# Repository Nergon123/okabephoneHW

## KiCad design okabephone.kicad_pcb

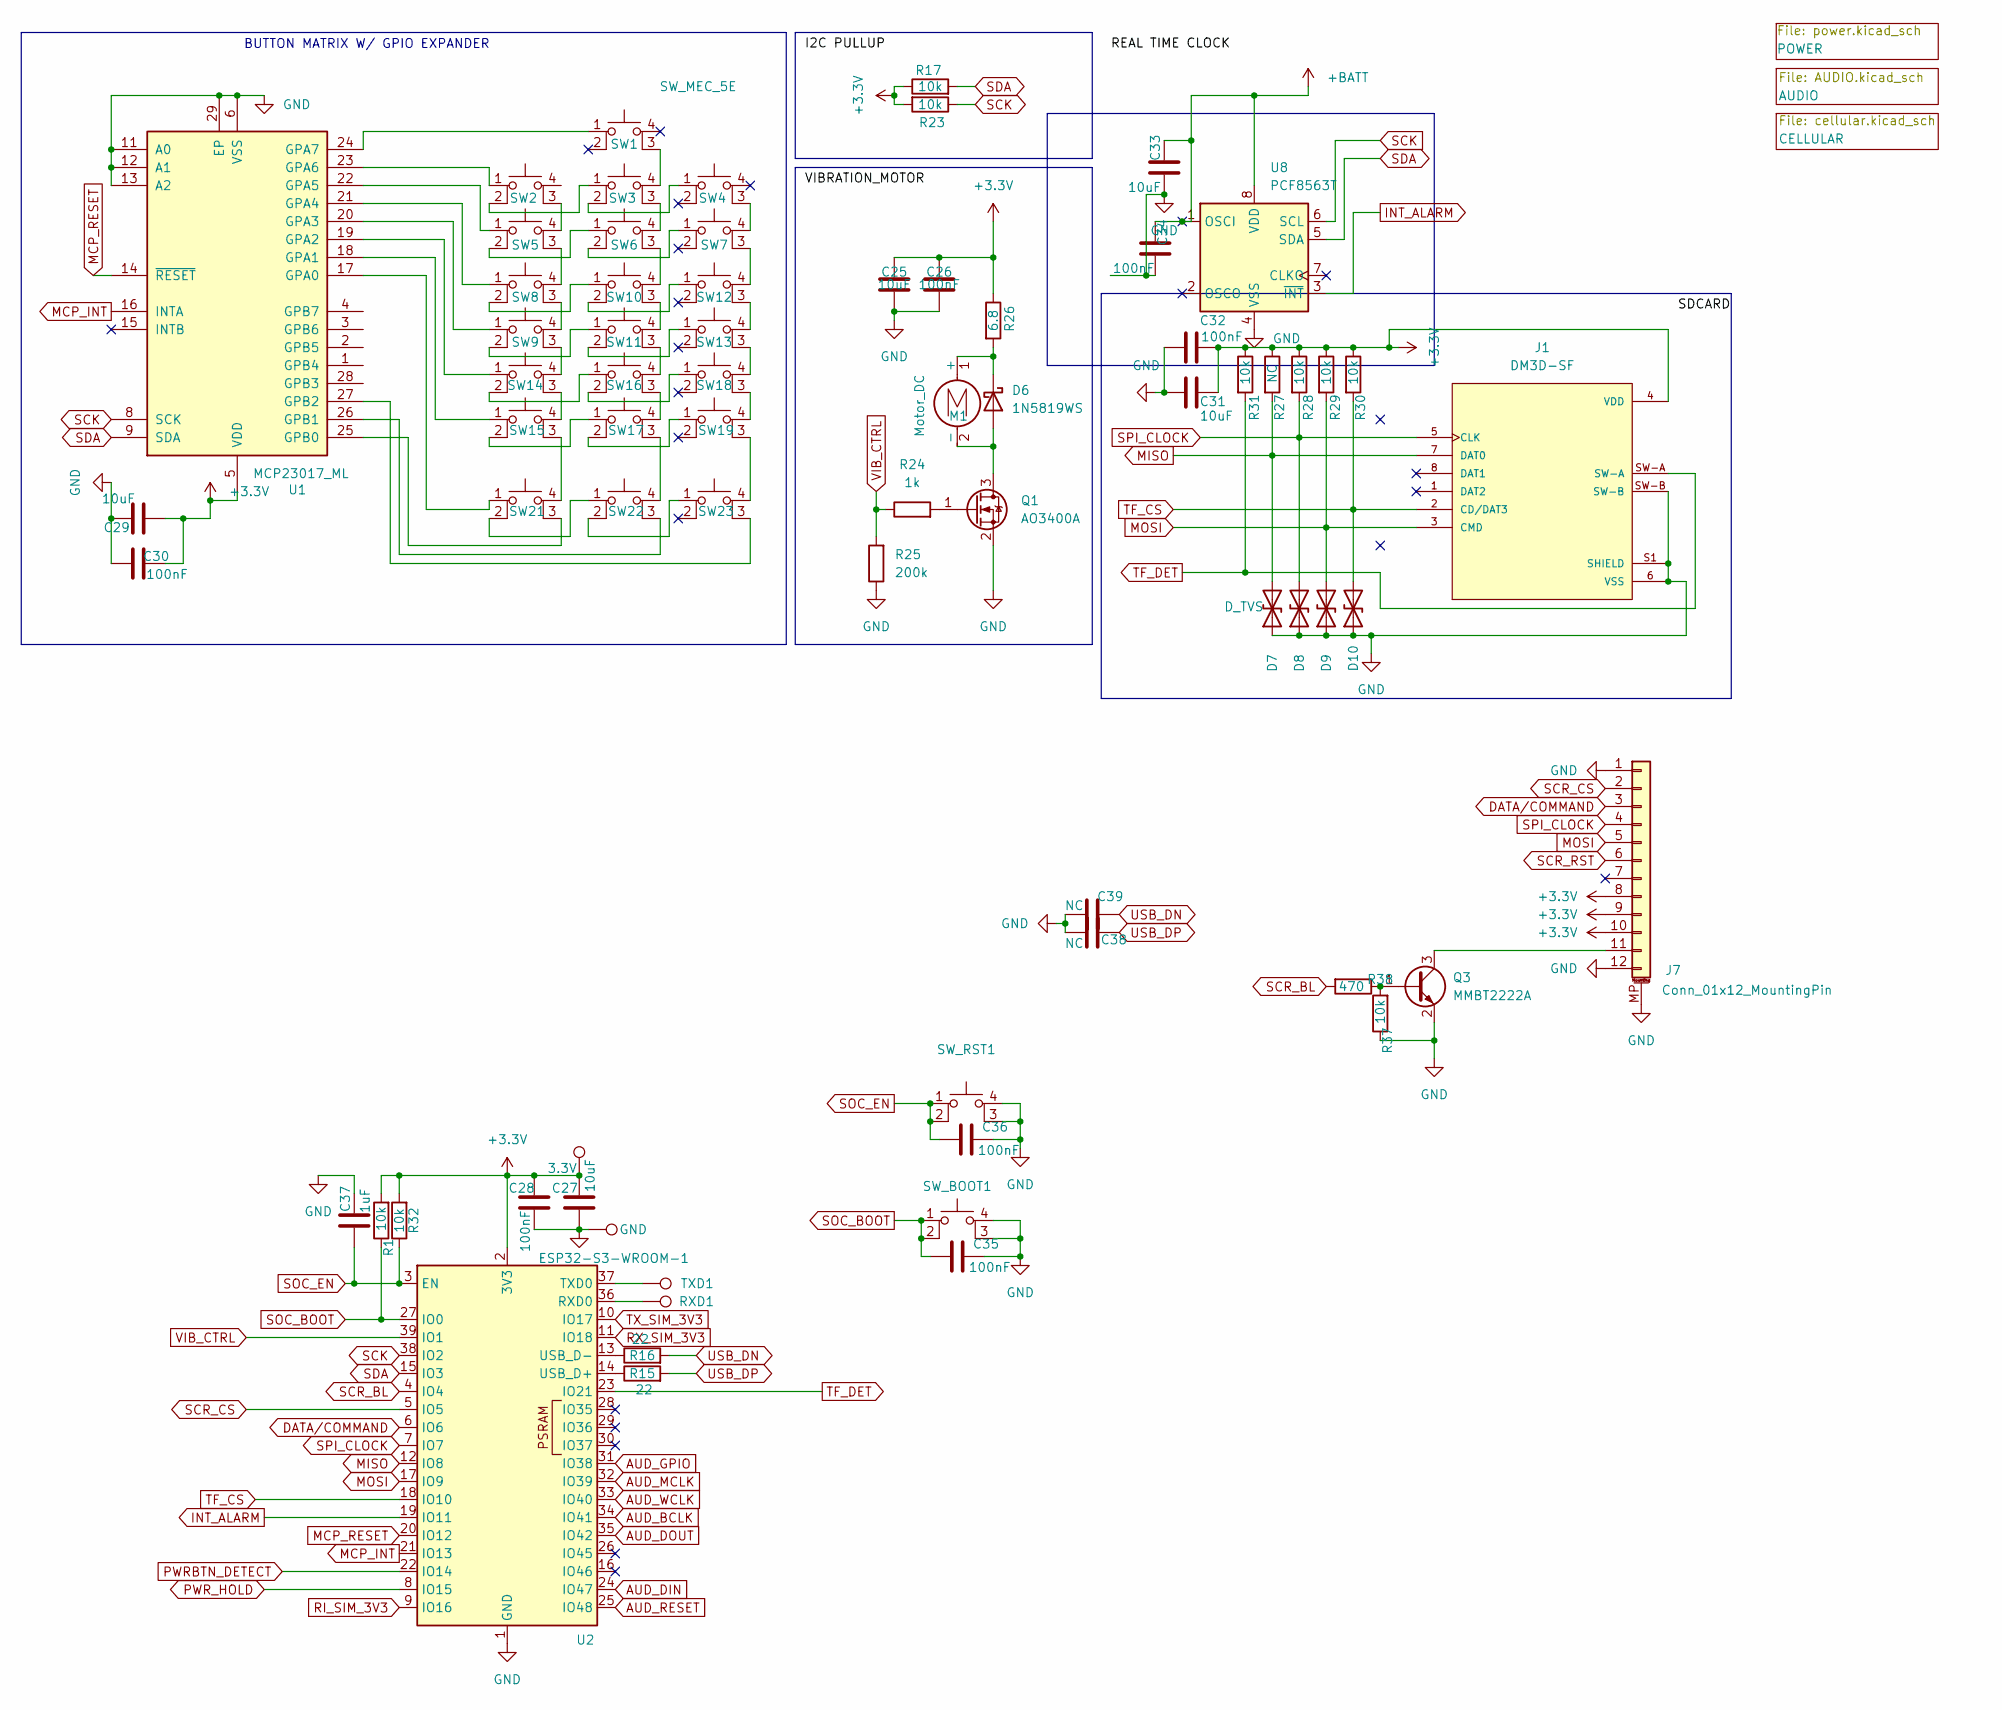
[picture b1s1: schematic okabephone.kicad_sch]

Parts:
C25, C27, C29, C31, C33: 10uF; C_0603_1608Metric_Pad1.08x0.95mm_HandSolder
C26, C28, C30, C32, C34, C35, C36: 100nF; C_0603_1608Metric_Pad1.08x0.95mm_HandSolder
C37: 1uF; C_0603_1608Metric_Pad1.08x0.95mm_HandSolder
C38, C39: NC; C_0603_1608Metric_Pad1.08x0.95mm_HandSolder
D6: 1N5819WS; D_SOD-323
D7, D8, D9, D10: D_TVS; D_0603_1608Metric_Pad1.05x0.95mm_HandSolder
J1: DM3D-SF; HRS_DM3D-SF; PARTREV 2017.1
J7: Conn_01x12_MountingPin; TE_1-1734839-2_1x12-1MP_P0.5mm_Horizontal
M1: Motor_DC; JST_EH_B2B-EH-A_1x02_P2.50mm_Vertical
Q1: AO3400A; SOT-23
Q3: MMBT2222A; SOT-23
R1, R17, R23, R28, R29, R30, R31, R32, R37: 10k; R_0603_1608Metric_Pad0.98x0.95mm_HandSolder
R15, R16: 22; R_0603_1608Metric_Pad0.98x0.95mm_HandSolder
R24: 1k; R_0603_1608Metric_Pad0.98x0.95mm_HandSolder
R25: 200k; R_0603_1608Metric_Pad0.98x0.95mm_HandSolder
R26: 6.8; R_0603_1608Metric_Pad0.98x0.95mm_HandSolder
R27: NC; R_0603_1608Metric_Pad0.98x0.95mm_HandSolder
R38: 470; R_0603_1608Metric_Pad0.98x0.95mm_HandSolder
RXD1: TestPoint; TestPoint_Pad_D1.0mm
SW1, SW2, SW3, SW4, SW5, SW6, SW7, SW8, SW9, SW10, SW11, SW12, SW13, SW14, SW15, SW16, SW17, SW18, SW19, SW21, SW22, SW23: SW_MEC_5E; SW_PTS526_SM08_SMTR2_LFS
SW_BOOT1: SW_MEC_5E; SW_PTS526_SM08_SMTR2_LFS
SW_RST1: SW_MEC_5E; SW_PTS526_SM08_SMTR2_LFS
TP8: 3.3V; TestPoint_Pad_D1.0mm
TP9: GND; TestPoint_Pad_D1.0mm
TXD1: TestPoint; TestPoint_Pad_D1.0mm
U1: MCP23017_ML; QFN-28-1EP_6x6mm_P0.65mm_EP4.25x4.25mm
U2: ESP32-S3-WROOM-1
U8: PCF8563T; SOIC-8_3.9x4.9mm_P1.27mm

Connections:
+3.3V: C25.2, C26.2, C27.2, C28.2, C29.2, C30.2, C31.2, C32.2, J1.4 (VDD), J7.8, J7.9, J7.10, R1.2, R17.1, R23.2, R26.1, R27.1, R28.1, R29.1, R30.1, R31.1, R32.2, TP8.1, U1.5 (VDD), U2.2 (3V3); also elsewhere on the board
+BATT: C33.2, C34.2, U8.1 (OSCI), U8.8 (VDD); also elsewhere on the board
AUD_BCLK: U2.34 (IO41); also elsewhere on the board
AUD_DIN: U2.24 (IO47); also elsewhere on the board
AUD_DOUT: U2.35 (IO42); also elsewhere on the board
AUD_GPIO: U2.31 (IO38); also elsewhere on the board
AUD_MCLK: U2.32 (IO39); also elsewhere on the board
AUD_RESET: U2.25 (IO48); also elsewhere on the board
AUD_WCLK: U2.33 (IO40); also elsewhere on the board
DATA/COMMAND: J7.3, U2.6 (IO6)
GND: C25.1, C26.1, C27.1, C28.1, C29.1, C30.1, C31.1, C32.1, C33.1, C34.1, C35.1, C36.1, C37.1, C38.1, C39.1, D7.1 (A1), D8.1 (A1), D9.1 (A1), D10.1 (A1), J1.6 (VSS), J1.S1 (SHIELD), J1.S2 (SHIELD), J1.S3 (SHIELD), J1.S4 (SHIELD), J1.SW-B, J7.1, J7.12, J7.MP (MountPin), Q1.2 (S), Q3.2 (E), R25.1, R37.1, SW_BOOT1.3 (K), SW_BOOT1.4 (A), SW_RST1.3 (K), SW_RST1.4 (A), TP9.1, U1.6 (VSS), U1.11 (A0), U1.12 (A1), U1.13 (A2), U1.29 (EP), U2.1 (GND), U2.40 (GND), U2.41 (GND), U8.4 (VSS); also elsewhere on the board
INT_ALARM: U2.19 (IO11), U8.3 (~INT)
MCP_INT: U1.16 (INTA), U2.21 (IO13)
MCP_RESET: U1.14 (~RESET), U2.20 (IO12)
MISO: D7.2 (A2), J1.7 (DAT0), R27.2, U2.12 (IO8)
MOSI: D9.2 (A2), J1.3 (CMD), J7.5, R29.2, U2.17 (IO9)
unnamed: D6.2 (A), M1.2 (-), Q1.3 (D)
unnamed: D6.1 (K), M1.1 (+), R26.2
unnamed: J7.11, Q3.3 (C)
unnamed: Q1.1 (G), R24.2
unnamed: Q3.1 (B), R37.2, R38.1
unnamed: SW1.3 (K), SW3.4 (A)
unnamed: SW2.3 (K), SW5.4 (A)
unnamed: SW2.2, SW3.1
unnamed: SW3.3 (K), SW6.4 (A)
unnamed: SW3.2, SW4.1
unnamed: SW4.3 (K), SW7.4 (A)
unnamed: SW5.3 (K), SW8.4 (A)
unnamed: SW5.2, SW6.1
unnamed: SW6.2, SW7.1
unnamed: SW8.3 (K), SW9.4 (A)
unnamed: SW6.3 (K), SW10.4 (A)
unnamed: SW10.3 (K), SW11.4 (A)
unnamed: SW8.2, SW10.1
unnamed: SW10.2, SW12.1
unnamed: SW11.3 (K), SW16.4 (A)
unnamed: SW9.2, SW11.1
unnamed: SW11.2, SW13.1
unnamed: SW7.3 (K), SW12.4 (A)
unnamed: SW12.3 (K), SW13.4 (A)
unnamed: SW13.3 (K), SW18.4 (A)
unnamed: SW9.3 (K), SW14.4 (A)
unnamed: SW14.3 (K), SW15.4 (A)
unnamed: SW14.2, SW16.1
unnamed: SW15.3 (K), SW21.4 (A)
unnamed: SW15.2, SW17.1
unnamed: SW16.3 (K), SW17.4 (A)
unnamed: SW16.2, SW18.1
unnamed: SW17.3 (K), SW22.4 (A)
unnamed: SW17.2, SW19.1
unnamed: SW18.3 (K), SW19.4 (A)
unnamed: SW19.3 (K), SW23.4 (A)
unnamed: SW21.3 (K), U1.25 (GPB0)
unnamed: SW21.2, SW22.1
unnamed: SW22.3 (K), U1.26 (GPB1)
unnamed: SW22.2, SW23.1
unnamed: SW23.3 (K), U1.27 (GPB2)
unnamed: SW21.1, U1.17 (GPA0)
unnamed: SW15.1, U1.18 (GPA1)
unnamed: SW14.1, U1.19 (GPA2)
unnamed: SW9.1, U1.20 (GPA3)
unnamed: SW8.1, U1.21 (GPA4)
unnamed: SW5.1, U1.22 (GPA5)
unnamed: SW2.1, U1.23 (GPA6)
unnamed: SW1.1, U1.24 (GPA7)
unnamed: RXD1.1, U2.36 (RXD0)
unnamed: TXD1.1, U2.37 (TXD0)
unnamed: R15.1, U2.14 (USB_D+)
unnamed: R16.1, U2.13 (USB_D-)
PWRBTN_DETECT: U2.22 (IO14); also elsewhere on the board
PWR_HOLD: U2.8 (IO15); also elsewhere on the board
RI_SIM_3V3: U2.9 (IO16); also elsewhere on the board
RX_SIM_3V3: U2.11 (IO18); also elsewhere on the board
SCK: R23.1, U1.8 (SCK), U2.38 (IO2), U8.6 (SCL); also elsewhere on the board
SCR_BL: R38.2, U2.4 (IO4)
SCR_CS: J7.2, U2.5 (IO5)
SCR_RST: J7.6
SDA: R17.2, U1.9 (SDA), U2.15 (IO3), U8.5 (SDA); also elsewhere on the board
SOC_BOOT: C35.2, R1.1, SW_BOOT1.1, SW_BOOT1.2, U2.27 (IO0)
SOC_EN: C36.2, C37.2, R32.1, SW_RST1.1, SW_RST1.2, U2.3 (EN)
SPI_CLOCK: D8.2 (A2), J1.5 (CLK), J7.4, R28.2, U2.7 (IO7)
TF_CS: D10.2 (A2), J1.2 (CD/DAT3), R30.2, U2.18 (IO10)
TF_DET: J1.SW-A, R31.2, U2.23 (IO21)
TX_SIM_3V3: U2.10 (IO17); also elsewhere on the board
USB_DN: C39.2, R16.2; also elsewhere on the board
USB_DP: C38.2, R15.2; also elsewhere on the board
VIB_CTRL: R24.1, R25.2, U2.39 (IO1)

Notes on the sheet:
BUTTON MATRIX W/ GPIO EXPANDER

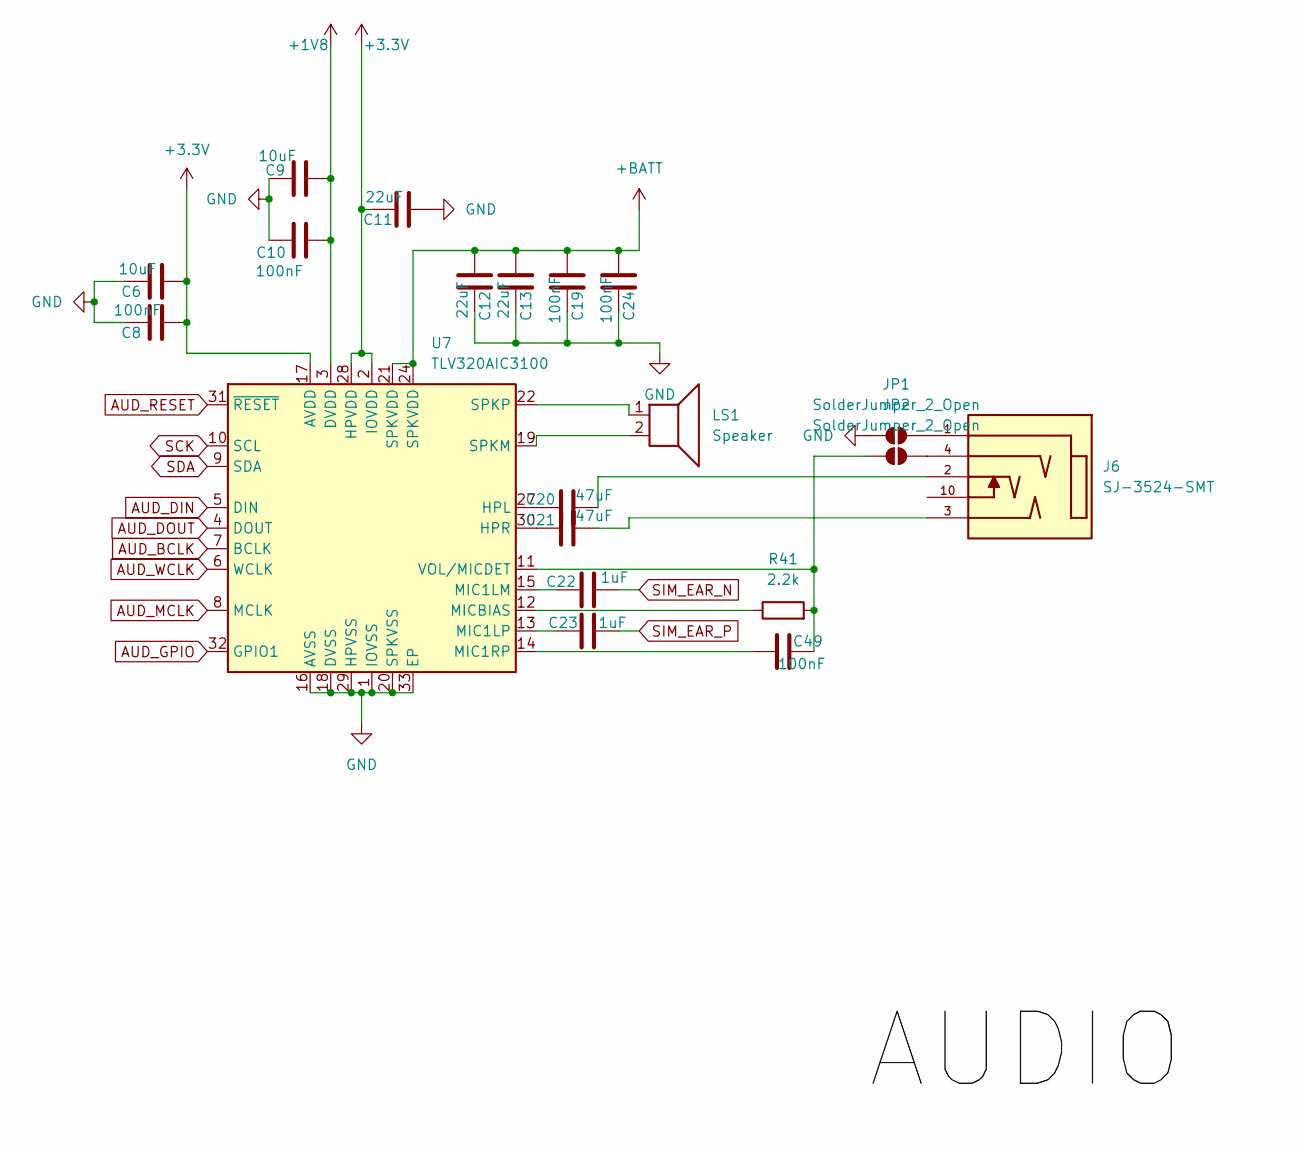
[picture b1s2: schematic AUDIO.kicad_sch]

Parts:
C6, C9: 10uF; C_0603_1608Metric_Pad1.08x0.95mm_HandSolder
C8, C10, C19, C24, C49: 100nF; C_0603_1608Metric_Pad1.08x0.95mm_HandSolder
C11, C12, C13: 22uF; C_0603_1608Metric_Pad1.08x0.95mm_HandSolder
C20, C21: 47uF; C_0603_1608Metric_Pad1.08x0.95mm_HandSolder
C22, C23: 1uF; C_0603_1608Metric_Pad1.08x0.95mm_HandSolder
J6: SJ-3524-SMT; SWITCHCRAFT_35RASMT6CHNTRX; PARTREV A
JP1, JP2: SolderJumper_2_Open; SolderJumper-2_P1.3mm_Open_TrianglePad1.0x1.5mm
LS1: Speaker; JST_EH_B2B-EH-A_1x02_P2.50mm_Vertical
R41: 2.2k
U7: TLV320AIC3100; VQFN-32-1EP_5x5mm_P0.5mm_EP3.5x3.5mm

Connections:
+1V8: C9.2, C10.2, U7.3 (DVDD); also elsewhere on the board
+3.3V: C6.2, C8.2, C11.1, U7.2 (IOVDD), U7.17 (AVDD), U7.28 (HPVDD); also elsewhere on the board
+BATT: C12.2, C13.2, C19.2, C24.2, U7.21 (SPKVDD), U7.24 (SPKVDD); also elsewhere on the board
AUD_BCLK: U7.7 (BCLK); also elsewhere on the board
AUD_DIN: U7.5 (DIN); also elsewhere on the board
AUD_DOUT: U7.4 (DOUT); also elsewhere on the board
AUD_GPIO: U7.32 (GPIO1); also elsewhere on the board
AUD_MCLK: U7.8 (MCLK); also elsewhere on the board
AUD_RESET: U7.31 (~RESET); also elsewhere on the board
AUD_WCLK: U7.6 (WCLK); also elsewhere on the board
GND: C6.1, C8.1, C9.1, C10.1, C11.2, C12.1, C13.1, C19.1, C24.1, J6.1, JP1.1 (A), JP1.2 (B), U7.1 (IOVSS), U7.16 (AVSS), U7.18 (DVSS), U7.20 (SPKVSS), U7.25 (SPKVSS), U7.29 (HPVSS), U7.33 (EP); also elsewhere on the board
unnamed: C20.2, J6.2
unnamed: C21.2, J6.3
unnamed: C49.1, JP2.1 (A), R41.2, U7.11 (VOL/MICDET)
unnamed: C49.2, U7.14 (MIC1RP)
unnamed: J6.4, JP2.2 (B)
unnamed: LS1.1, U7.22 (SPKP), U7.26 (SPKP)
unnamed: LS1.2, U7.19 (SPKM), U7.23 (SPKM)
unnamed: R41.1, U7.12 (MICBIAS)
unnamed: C20.1, U7.27 (HPL)
unnamed: C21.1, U7.30 (HPR)
unnamed: C22.1, U7.15 (MIC1LM)
unnamed: C23.1, U7.13 (MIC1LP)
SCK: U7.10 (SCL); also elsewhere on the board
SDA: U7.9 (SDA); also elsewhere on the board
SIM_EAR_N: C22.2; also elsewhere on the board
SIM_EAR_P: C23.2; also elsewhere on the board

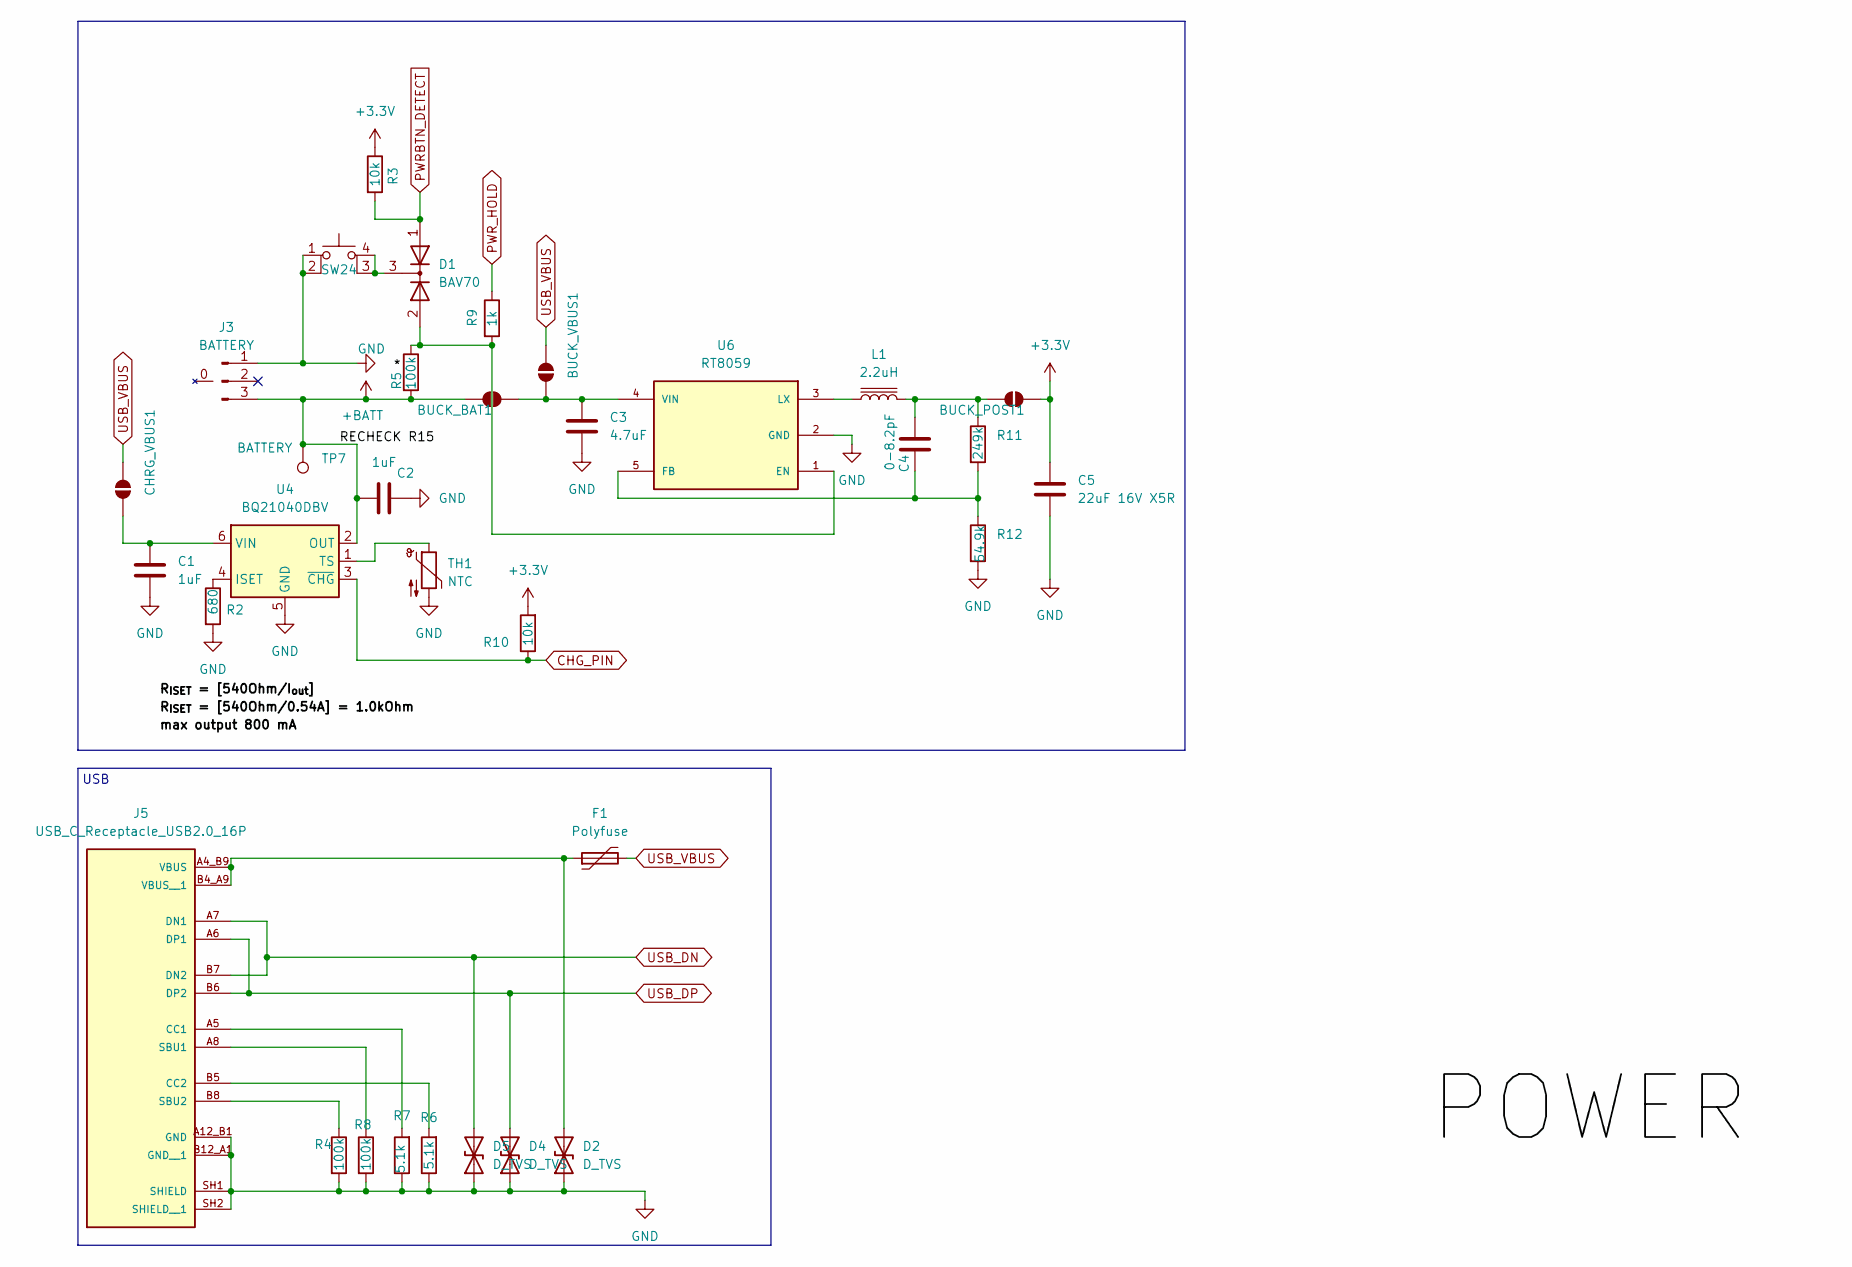
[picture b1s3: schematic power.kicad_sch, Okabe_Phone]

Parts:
BUCK_BAT1: SolderJumper_2_Open; SolderJumper-2_P1.3mm_Open_Pad1.0x1.5mm
BUCK_POST1: SolderJumper_2_Open; SolderJumper-2_P1.3mm_Open_Pad1.0x1.5mm
BUCK_VBUS1: SolderJumper_2_Open; SolderJumper-2_P1.3mm_Open_Pad1.0x1.5mm
C1, C2: 1uF; C_0603_1608Metric_Pad1.08x0.95mm_HandSolder
C3: 4.7uF; C_0603_1608Metric_Pad1.08x0.95mm_HandSolder
C4: 0-8.2pF; C_0603_1608Metric_Pad1.08x0.95mm_HandSolder
C5: 22uF 16V X5R; C_1206_3216Metric
CHRG_VBUS1: SolderJumper_2_Open; SolderJumper-2_P1.3mm_Open_Pad1.0x1.5mm
D1: BAV70; SOT-23
D2, D4, D5: D_TVS; D_0603_1608Metric_Pad1.05x0.95mm_HandSolder
F1: Polyfuse; Fuse_1210_3225Metric
J3: BATTERY; Battery connector 3mm nergon
J5: USB_C_Receptacle_USB2.0_16P; CUI_UJ20-C-G-MSMT-TR-68; PARTREV 1.0
L1: 2.2uH; L_6.3x6.3_H3
R2: 680; R_0603_1608Metric_Pad0.98x0.95mm_HandSolder
R3, R10: 10k; R_0603_1608Metric_Pad0.98x0.95mm_HandSolder
R4, R5, R8: 100k; R_0603_1608Metric_Pad0.98x0.95mm_HandSolder
R6, R7: 5.1k; R_0603_1608Metric_Pad0.98x0.95mm_HandSolder
R9: 1k; R_0603_1608Metric_Pad0.98x0.95mm_HandSolder
R11: 249k; R_0603_1608Metric_Pad0.98x0.95mm_HandSolder
R12: 54.9k; R_0603_1608Metric_Pad0.98x0.95mm_HandSolder
SW24: SW_MEC_5E; SW_PTS526_SM08_SMTR2_LFS
TH1: NTC; JST_EH_B2B-EH-A_1x02_P2.50mm_Vertical
TP7: BATTERY; TestPoint_Pad_D1.0mm
U4: BQ21040DBV; SOT-23-6
U6: RT8059; TSOT-23-5_HandSoldering

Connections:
+3.3V: BUCK_POST1.1 (A), C5.1, R3.1, R10.2; also elsewhere on the board
+BATT: BUCK_BAT1.2 (B), C2.1, J3.3, R5.2, TP7.1, U4.2 (OUT); also elsewhere on the board
CHG_PIN: R10.1, U4.3 (~CHG)
GND: C1.2, C2.2, C3.2, C5.2, D2.1 (A1), D4.1 (A1), D5.1 (A1), J3.1, J5.A12_B1 (GND), J5.B12_A1 (GND__1), J5.SH1 (SHIELD), J5.SH2 (SHIELD__1), R2.2, R4.2, R6.1, R7.1, R8.2, R12.2, SW24.1, SW24.2, TH1.2, U4.5 (GND), U6.2 (GND); also elsewhere on the board
unnamed: BUCK_BAT1.1 (A), BUCK_VBUS1.2 (B), C3.1, U6.4 (VIN)
unnamed: BUCK_POST1.2 (B), C4.1, L1.2, R11.1
unnamed: C1.1, CHRG_VBUS1.2 (B), U4.6 (VIN)
unnamed: D1.3 (K), SW24.3 (K), SW24.4 (A)
unnamed: D2.2 (A2), F1.1, J5.A4_B9 (VBUS), J5.B4_A9 (VBUS__1)
unnamed: J5.A5 (CC1), R7.2
unnamed: J5.B5 (CC2), R6.2
unnamed: J5.A8 (SBU1), R8.1
unnamed: J5.B8 (SBU2), R4.1
unnamed: R2.1, U4.4 (ISET)
unnamed: TH1.1, U4.1 (TS)
unnamed: D1.2 (A), R5.1, R9.2, U6.1 (EN)
unnamed: C4.2, R11.2, R12.1, U6.5 (FB)
unnamed: L1.1, U6.3 (LX)
PWRBTN_DETECT: D1.1 (A), R3.2; also elsewhere on the board
PWR_HOLD: R9.1; also elsewhere on the board
USB_DN: D5.2 (A2), J5.A7 (DN1), J5.B7 (DN2); also elsewhere on the board
USB_DP: D4.2 (A2), J5.A6 (DP1), J5.B6 (DP2); also elsewhere on the board
USB_VBUS: BUCK_VBUS1.1 (A), CHRG_VBUS1.1 (A), F1.2

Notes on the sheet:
USB

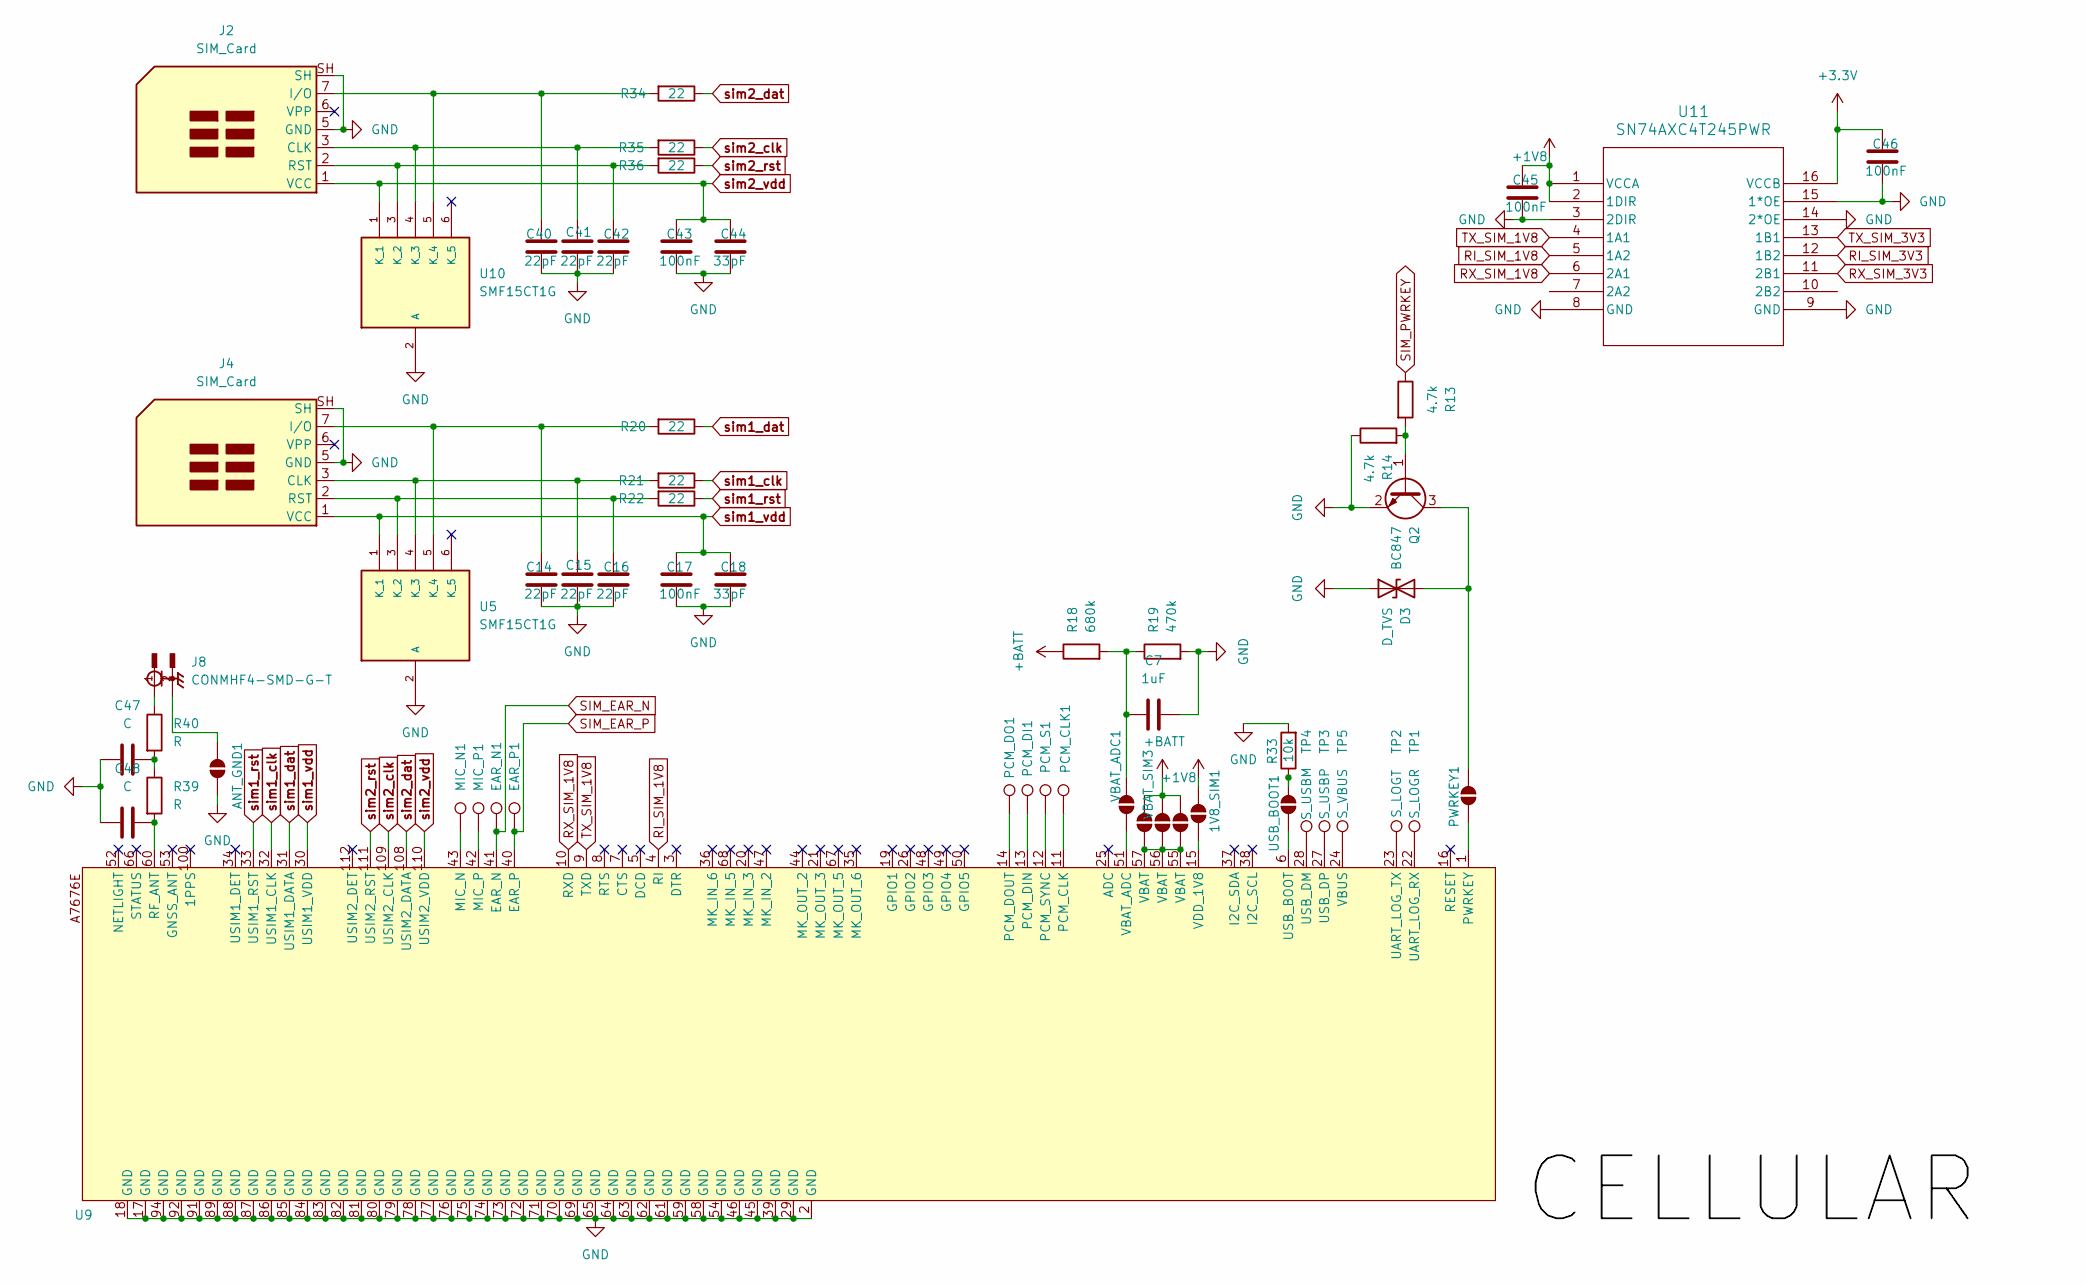
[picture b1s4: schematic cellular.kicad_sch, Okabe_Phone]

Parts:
1V8_SIM1: SolderJumper_2_Open; SolderJumper-2_P1.3mm_Open_Pad1.0x1.5mm
ANT_GND1: SolderJumper_2_Open; SolderJumper-2_P1.3mm_Open_Pad1.0x1.5mm
C7: 1uF; C_0603_1608Metric_Pad1.08x0.95mm_HandSolder
C14, C15, C16, C40, C41, C42: 22pF; C_0603_1608Metric_Pad1.08x0.95mm_HandSolder
C17, C43, C45, C46: 100nF; C_0603_1608Metric_Pad1.08x0.95mm_HandSolder
C18, C44: 33pF; C_0603_1608Metric_Pad1.08x0.95mm_HandSolder
C47, C48: C; C_0603_1608Metric_Pad1.08x0.95mm_HandSolder
D3: D_TVS; D_0603_1608Metric_Pad1.05x0.95mm_HandSolder
EAR_N1: TestPoint; TestPoint_Pad_D1.5mm
EAR_P1: TestPoint; TestPoint_Pad_D1.5mm
J2, J4: SIM_Card; nanoSIM_GCT_SIM8060-6-0-14-00
J8: CONMHF4-SMD-G-T; TE_CONMHF4-SMD-G-T; PARTREV A
MIC_N1: TestPoint; TestPoint_Pad_D1.5mm
MIC_P1: TestPoint; TestPoint_Pad_D1.5mm
PCM_CLK1: TestPoint; TestPoint_Pad_D1.0mm
PCM_DI1: TestPoint; TestPoint_Pad_D1.0mm
PCM_DO1: TestPoint; TestPoint_Pad_D1.0mm
PCM_S1: TestPoint; TestPoint_Pad_D1.0mm
PWRKEY1: SolderJumper_2_Open; SolderJumper-2_P1.3mm_Open_Pad1.0x1.5mm
Q2: BC847; SOT-23
R13, R14: 4.7k; R_0603_1608Metric_Pad0.98x0.95mm_HandSolder
R18: 680k; R_0603_1608Metric_Pad0.98x0.95mm_HandSolder
R19: 470k; R_0603_1608Metric_Pad0.98x0.95mm_HandSolder
R20, R21, R22, R34, R35, R36: 22; R_0603_1608Metric_Pad0.98x0.95mm_HandSolder
R33: 10k; R_0603_1608Metric_Pad0.98x0.95mm_HandSolder
R39, R40: R; R_0603_1608Metric_Pad0.98x0.95mm_HandSolder
TP1: S_LOGR; TestPoint_Pad_D1.0mm
TP2: S_LOGT; TestPoint_Pad_D1.0mm
TP3: S_USBP; TestPoint_Pad_D1.0mm
TP4: S_USBM; TestPoint_Pad_D1.0mm
TP5: S_VBUS; TestPoint_Pad_D1.0mm
U5, U10: SMF15CT1G; SOT65P210X110-6N; M_PART_NUMBER SMF15CT1G
U9: XCVR_A7672SA__LASE_
U11: SN74AXC4T245PWR; TSSOP16_PW_TEX
USB_BOOT1: SolderJumper_2_Open; SolderJumper-2_P1.3mm_Open_Pad1.0x1.5mm
VBAT_ADC1: SolderJumper_2_Open; SolderJumper-2_P1.3mm_Open_Pad1.0x1.5mm
VBAT_SIM1, VBAT_SIM2, VBAT_SIM3: SolderJumper_2_Open; SolderJumper-2_P1.3mm_Open_Pad1.0x1.5mm

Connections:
+1V8: 1V8_SIM1.2 (B), C45.1, U11.1 (VCCA), U11.2 (1DIR); also elsewhere on the board
+3.3V: C46.1, U11.16 (VCCB); also elsewhere on the board
+BATT: R18.1, VBAT_SIM1.2 (B), VBAT_SIM2.2 (B), VBAT_SIM3.2 (B); also elsewhere on the board
GND: ANT_GND1.1 (A), C7.2, C14.2, C15.2, C16.2, C17.2, C18.2, C40.2, C41.2, C42.2, C43.2, C44.2, C45.2, C46.2, C47.1, C48.1, D3.1 (A1), J2.5 (GND), J2.SH, J4.5 (GND), J4.SH, Q2.2 (E), R14.1, R19.2, R33.2, U5.2 (A), U9.2 (GND), U9.17 (GND), U9.18 (GND), U9.29 (GND), U9.39 (GND), U9.45 (GND), U9.46 (GND), U9.54 (GND), U9.58 (GND), U9.59 (GND), U9.61 (GND), U9.62 (GND), U9.63 (GND), U9.64 (GND), U9.65 (GND), U9.69 (GND), U9.70 (GND), U9.71 (GND), U9.72 (GND), U9.73 (GND), U9.74 (GND), U9.75 (GND), U9.76 (GND), U9.77 (GND), U9.78 (GND), U9.79 (GND), U9.80 (GND), U9.81 (GND), U9.82 (GND), U9.83 (GND), U9.84 (GND), U9.85 (GND), U9.86 (GND), U9.87 (GND), U9.88 (GND), U9.89 (GND), U9.91 (GND), U9.92 (GND), U9.94 (GND), U10.2 (A), U11.3 (2DIR), U11.8 (GND), U11.9 (GND), U11.14 (2*OE), U11.15 (1*OE); also elsewhere on the board
unnamed: 1V8_SIM1.1 (A), U9.15 (VDD_1V8)
unnamed: C47.2, R39.1, R40.2
unnamed: D3.2 (A2), PWRKEY1.2 (B), Q2.3 (C)
unnamed: C41.1, J2.3 (CLK), R35.2, U10.4 (K_3)
unnamed: C40.1, J2.7 (I/O), R34.2, U10.5 (K_4)
unnamed: C42.1, J2.2 (RST), R36.2, U10.3 (K_2)
unnamed: C15.1, J4.3 (CLK), R21.2, U5.4 (K_3)
unnamed: C14.1, J4.7 (I/O), R20.2, U5.5 (K_4)
unnamed: C16.1, J4.2 (RST), R22.2, U5.3 (K_2)
unnamed: J8.1, R40.1
unnamed: PWRKEY1.1 (A), U9.1 (PWRKEY)
unnamed: Q2.1 (B), R13.2, R14.2
unnamed: MIC_N1.1, U9.43 (MIC_N)
unnamed: MIC_P1.1, U9.42 (MIC_P)
unnamed: PCM_CLK1.1, U9.11 (PCM_CLK)
unnamed: PCM_DI1.1, U9.13 (PCM_DIN)
unnamed: PCM_DO1.1, U9.14 (PCM_DOUT)
unnamed: PCM_S1.1, U9.12 (PCM_SYNC)
unnamed: C48.2, R39.2, U9.60 (RF_ANT)
unnamed: TP1.1, U9.22 (UART_LOG_RX)
unnamed: TP2.1, U9.23 (UART_LOG_TX)
unnamed: U9.6 (USB_BOOT), USB_BOOT1.1 (A)
unnamed: TP4.1, U9.28 (USB_DM)
unnamed: TP3.1, U9.27 (USB_DP)
unnamed: U9.51 (VBAT_ADC), VBAT_ADC1.1 (A)
unnamed: TP5.1, U9.24 (VBUS)
unnamed: R33.1, USB_BOOT1.2 (B)
unnamed: C7.1, R18.2, R19.1, VBAT_ADC1.2 (B)
unnamed: U9.55 (VBAT), U9.56 (VBAT), U9.57 (VBAT), VBAT_SIM1.1 (A), VBAT_SIM2.1 (A), VBAT_SIM3.1 (A)
RI_SIM_1V8: U9.4 (RI), U11.5 (1A2)
RI_SIM_3V3: U11.12 (1B2); also elsewhere on the board
RX_SIM_1V8: U9.10 (RXD), U11.6 (2A1)
RX_SIM_3V3: U11.11 (2B1); also elsewhere on the board
SIM_EAR_N: EAR_N1.1, U9.41 (EAR_N); also elsewhere on the board
SIM_EAR_P: EAR_P1.1, U9.40 (EAR_P); also elsewhere on the board
SIM_PWRKEY: R13.1
TX_SIM_1V8: U9.9 (TXD), U11.4 (1A1)
TX_SIM_3V3: U11.13 (1B1); also elsewhere on the board
sim1_clk: R21.1, U9.32 (USIM1_CLK)
sim1_dat: R20.1, U9.31 (USIM1_DATA)
sim1_rst: R22.1, U9.33 (USIM1_RST)
sim1_vdd: C17.1, C18.1, J4.1 (VCC), U5.1 (K_1), U9.30 (USIM1_VDD)
sim2_clk: R35.1, U9.109 (USIM2_CLK)
sim2_dat: R34.1, U9.108 (USIM2_DATA)
sim2_rst: R36.1, U9.111 (USIM2_RST)
sim2_vdd: C43.1, C44.1, J2.1 (VCC), U9.110 (USIM2_VDD), U10.1 (K_1)
~: ANT_GND1.2 (B), J8.2, J8.3, J8.4

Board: 2 copper layers, 179 parts (41 on the bottom side), 154 nets, no tracks yet.

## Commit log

2026-01-10 init
2026-01-10 not init
2026-01-10 SD card and stuff?
2026-02-23 kicady
2026-02-23 battery polarity
2026-02-24 power
2026-02-28 spi joke
2026-03-01 buck converter
2026-03-02 eee:
2026-06-19 mblya
2026-06-21 SCHEMATIC
2026-06-21 SCHEMATIC2
2026-06-21 PCB BEGINNNING
2026-06-22 pcb progress
2026-06-22 what
